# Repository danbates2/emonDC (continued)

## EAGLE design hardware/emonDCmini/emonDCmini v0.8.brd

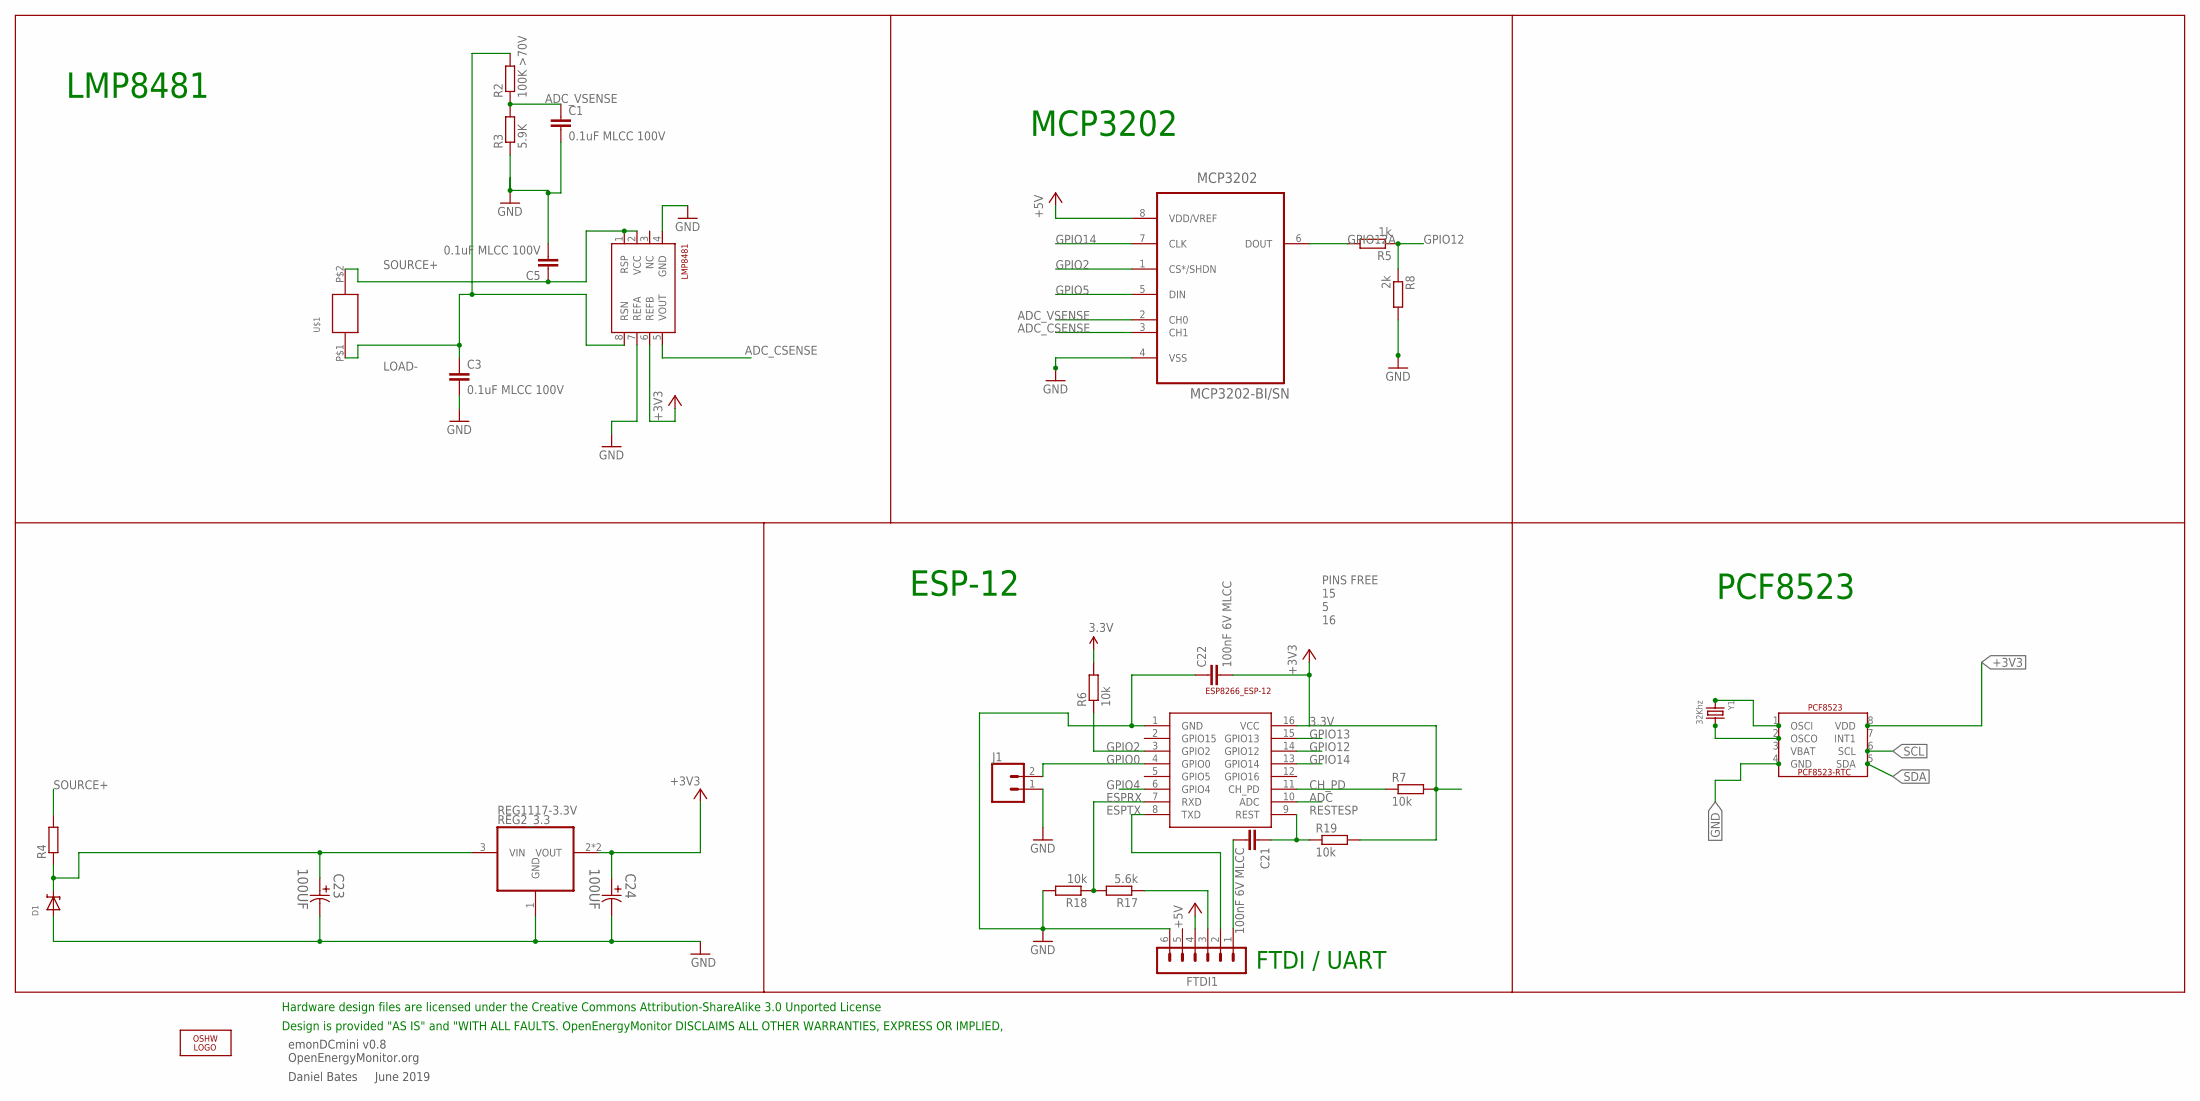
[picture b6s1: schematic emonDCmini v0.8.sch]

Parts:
C1, C3, C5: 0.1uF MLCC 100V; C0805
C21, C22: 100nF 6V MLCC; C0805
C23, C24: 100UF; CAPAE530X610N
D1: DIODE-ZENER; SMADIODE
ESP-12: ESP8266_ESP-12; ESP8266-ESP12
FTDI1: FTDI-ESP; MA06-1
J1: CONN_02; 1X02
LMP8481: LMP8481-H; S-PDSO-G08
LOGO1: OSHW_LOGO_6MILX0200-NT; OSHW_6X200_NOTEXT
MCP3202: MCP3202-BI/SN; SOIC127P600X175-8N
PCF8523: PCF8523_RTC; SOIC_8
R2: 100K >70V; R0603; MPN MCWR06X1003FTL
R3: 5.9K; R0603; MPN MCWR06X5901FTL
R4: R-EU_R2512; R2512
R5: 1k; R0603
R6, R7, R18, R19: 10k; R0603
R8: 2k; R0603
R17: 5.6k; R0603
REG2_3.3: REG1117-3.3V; SOT223; MPN REG1117-3.3
U$1: EBW_SERIES_10.5MM
Y1: 32Khz; CRYSTAL_8X3.8

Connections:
3.3V: C22.2, ESP-12.16 (VCC), LMP8481.6 (REFB), R6.2, R7.2, R19.2
6.5V: C23.1, D1.C, R4.1, REG2_3.3.3 (VIN)
+3V3: C24.1, PCF8523.8 (VDD), REG2_3.3.2 (VOUT), REG2_3.3.4 (VOUT)
+5V: FTDI1.4, MCP3202.8 (VDD/VREF)
ADC: ESP-12.10 (ADC)
ADC_CSENSE: LMP8481.5 (VOUT), MCP3202.3 (CH1)
ADC_VSENSE: C1.1, MCP3202.2 (CH0), R2.1, R3.2
CH_PD: ESP-12.11 (CH_PD), R7.1
ESPRX: ESP-12.7 (RXD), R17.2, R18.1
ESPTX: ESP-12.8 (TXD), FTDI1.2
GND: C1.2, C3.2, C5.2, C22.1, C23.2, C24.2, D1.A, ESP-12.1 (GND), FTDI1.6, J1.1, LMP8481.4 (GND), LMP8481.7 (REFA), MCP3202.4 (VSS), PCF8523.4 (GND), R3.1, R8.2, R18.2, REG2_3.3.1 (GND)
GPIO0: ESP-12.4 (GPIO0), J1.2
GPIO2: ESP-12.3 (GPIO2), MCP3202.1 (CS*/SHDN), R6.1
GPIO4: ESP-12.6 (GPIO4)
GPIO5: MCP3202.5 (DIN)
GPIO12: ESP-12.14 (GPIO12), R5.1, R8.1
GPIO12A: MCP3202.6 (DOUT), R5.2
GPIO13: ESP-12.15 (GPIO13)
GPIO14: ESP-12.13 (GPIO14), MCP3202.7 (CLK)
LOAD-: C3.1, LMP8481.8 (RSN), R2.2, U$1.P$1
unnamed: FTDI1.3, R17.1
unnamed: PCF8523.2 (OSCO), Y1.P$4 (2)
unnamed: PCF8523.1 (OSCI), Y1.P$1 (1)
RESTESP: C21.1, ESP-12.9 (REST), R19.1
RST: C21.2, FTDI1.1
SCL: PCF8523.6 (SCL)
SDA: PCF8523.5 (SDA)
SOURCE+: C5.1, LMP8481.1 (RSP), LMP8481.2 (VCC), R4.2, U$1.P$2

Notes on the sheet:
emonDCmini v0.8 OpenEnergyMonitor.org
Daniel Bates June 2019
Design is provided "AS IS" and "WITH ALL FAULTS. OpenEnergyMonitor DISCLAIMS ALL OTHER WARRANTIES, EXPRESS OR IMPLIED,
Hardware design files are licensed under the Creative Commons Attribution-ShareAlike 3.0 Unported License
LMP8481
ESP-12
PINS FREE 15 5 16
MCP3202
FTDI / UART
PCF8523

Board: 2 copper layers, 29 parts (9 on the bottom side), 22 nets, no tracks yet.

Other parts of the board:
U$3: DRAGON_LOGO_NOTEXT

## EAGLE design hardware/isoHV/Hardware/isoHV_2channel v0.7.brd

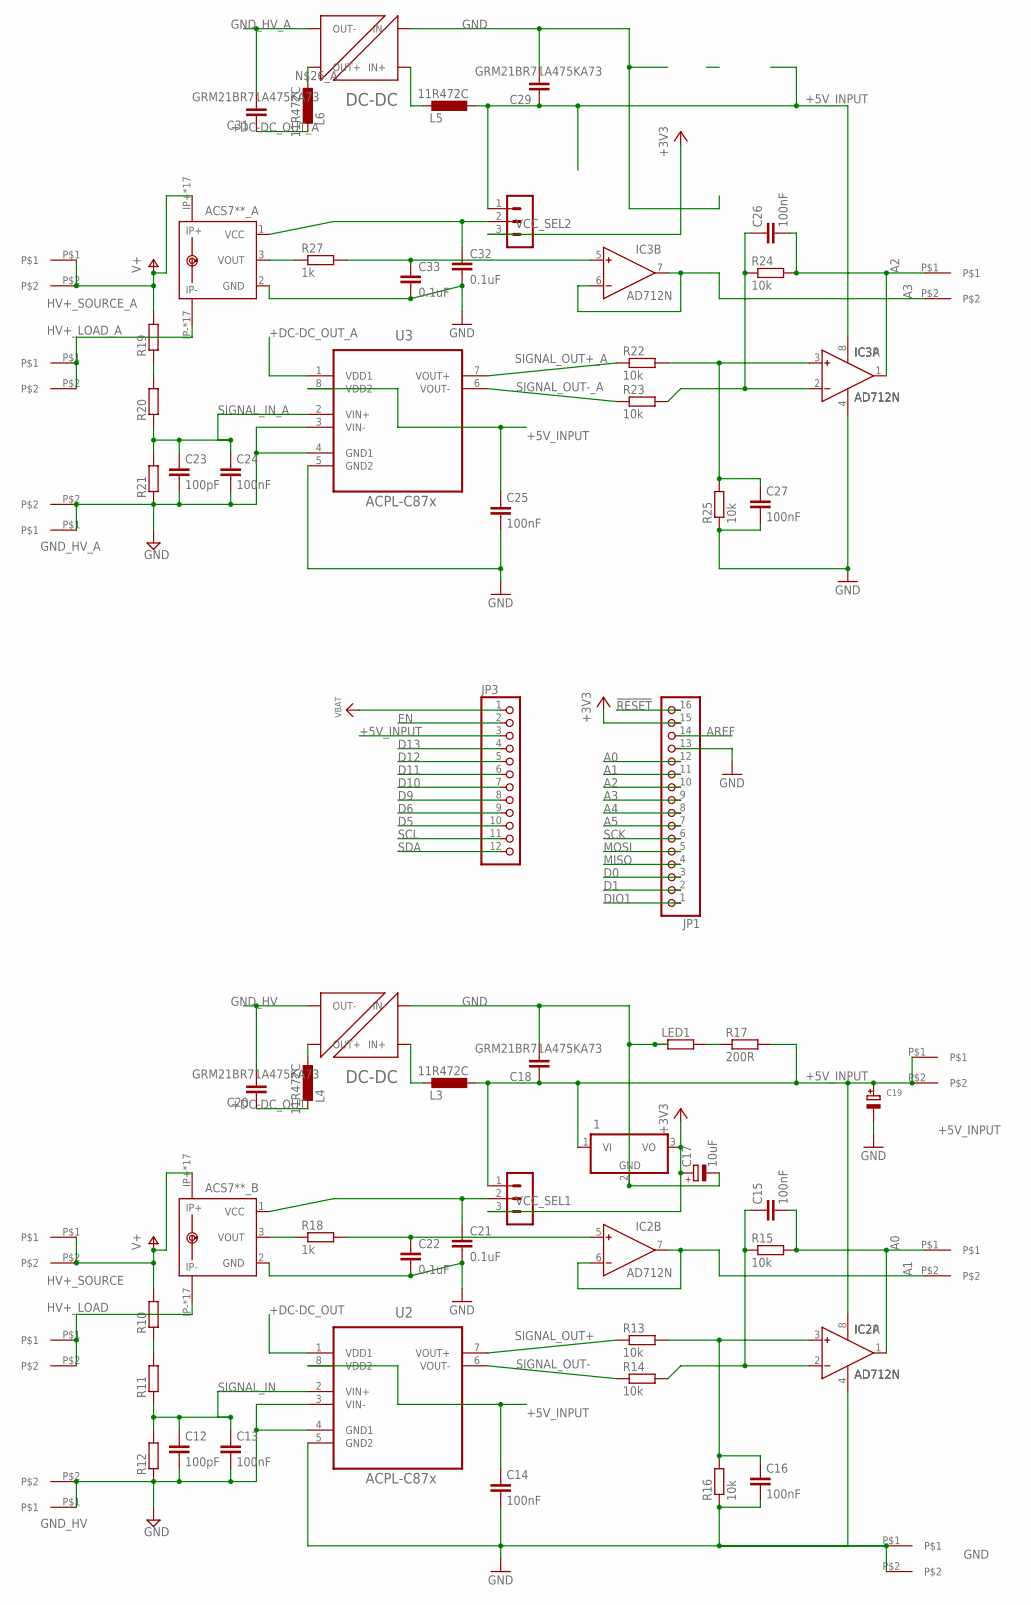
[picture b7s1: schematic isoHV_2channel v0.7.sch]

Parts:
1: 7805TV; TO220V
ACS7**_A, ACS7**_B: ACS758KCB-150B-PFF-T; CB-PFF; MPN ACS7**
C12, C23: 100pF; C025-025X050
C13, C14, C15, C16, C24, C25, C26, C27: 100nF; C025-025X050
C17: 10uF; B45181A
C18, C29: GRM21BR71A475KA73; C025-025X050
C19: CAP_ELECTROLYTICPTH_3.5MMGRID_10MMDIA; CELEC_3.5MM_10MM
C20, C31: GRM21BR71A475KA73; C025-050X050
C21, C22, C32, C33: 0.1uF; C025-025X050
IC2, IC3: AD712N; DIL08
JP1: HEADER-1X16ROUND; 1X16_ROUND
JP3: HEADER-1X12; 1X12_ROUND
L3, L4, L5, L6: 11R472C; 0204V
LED1: R-EU_0204/2V; 0204V
R10, R11, R12, R19, R20, R21: R-EU_0411/15; 0411/15
R13, R14, R15, R16, R22, R23, R24, R25: 10k; 0204/7
R17: 200R; 0204V
R18, R27: 1k; 0204/7
U2, U3: ACPL-C87x; SOIC127P1150X330-8N
U$8, U$9, U$10, U$14, U$15, U$16, U$21, U$22, U$25, U$26: 7.62MM_TERMINAL_BLOCK; 7.62MM
U$17, U$27: NXF1
VCC_SEL1, VCC_SEL2: MA03-1

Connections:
!RESET: JP1.16
+3V3: 1.3 (VO), C17.+, JP1.15, VCC_SEL1.3, VCC_SEL2.3
+5V_INPUT: 1.1 (VI), C14.1, C18.1, C19.+, C25.1, C29.1, IC2.8 (V+), IC3.8 (V+), JP3.3, L3.2, L5.2, R17.2, U2.8 (VDD2), U3.8 (VDD2), U$10.P$1, U$10.P$2, VCC_SEL1.1, VCC_SEL2.1
+DC-DC_OUT: C20.1, L4.1, U2.1 (VDD1)
+DC-DC_OUT_A: C31.1, L6.1, U3.1 (VDD1)
A0: C15.2, IC2.1 (OUT), JP1.12, R15.2, U$15.P$1
A1: IC2.6 (IN-), IC2.7 (OUT), JP1.11, U$15.P$2
A2: C26.2, IC3.1 (OUT), JP1.10, R24.2, U$25.P$1
A3: IC3.6 (IN-), IC3.7 (OUT), JP1.9, U$25.P$2
A4: JP1.8
A5: JP1.7
AREF: JP1.14
D0: JP1.3
D1: JP1.2
D5: JP3.10
D6: JP3.9
D9: JP3.8
D10: JP3.7
D11: JP3.6
D12: JP3.5
D13: JP3.4
DIO1: JP1.1
EN: JP3.2
GND: 1.2 (GND), ACS7**_A.2 (GND), ACS7**_B.2 (GND), C14.2, C16.2, C17.-, C18.2, C19.-, C21.2, C22.2, C25.2, C27.2, C29.2, C32.2, C33.2, IC2.4 (V-), IC3.4 (V-), JP1.13, LED1.1, R16.1, R25.1, U2.5 (GND2), U3.5 (GND2), U$14.P$1, U$14.P$2, U$17.P$1 (IN-), U$27.P$1 (IN-)
GND_HV: C12.2, C13.2, C20.2, R12.1, U2.3 (VIN-), U2.4 (GND1), U$9.P$1, U$9.P$2, U$17.P$7 (OUT-)
GND_HV_A: C23.2, C24.2, C31.2, R21.1, U3.3 (VIN-), U3.4 (GND1), U$22.P$1, U$22.P$2, U$27.P$7 (OUT-)
HV+_LOAD: ACS7**_B.IP-, ACS7**_B.IP-@2 (IP-), ACS7**_B.IP-@3 (IP-), ACS7**_B.IP-@4 (IP-), ACS7**_B.IP-@5 (IP-), ACS7**_B.IP-@6 (IP-), ACS7**_B.IP-@7 (IP-), ACS7**_B.IP-@8 (IP-), ACS7**_B.IP-@9 (IP-), ACS7**_B.IP-@10 (IP-), ACS7**_B.IP-@11 (IP-), ACS7**_B.IP-@12 (IP-), ACS7**_B.IP-@13 (IP-), ACS7**_B.IP-@14 (IP-), ACS7**_B.IP-@15 (IP-), ACS7**_B.IP-@16 (IP-), ACS7**_B.IP-@17 (IP-), U$16.P$1, U$16.P$2
HV+_LOAD_A: ACS7**_A.IP-, ACS7**_A.IP-@2 (IP-), ACS7**_A.IP-@3 (IP-), ACS7**_A.IP-@4 (IP-), ACS7**_A.IP-@5 (IP-), ACS7**_A.IP-@6 (IP-), ACS7**_A.IP-@7 (IP-), ACS7**_A.IP-@8 (IP-), ACS7**_A.IP-@9 (IP-), ACS7**_A.IP-@10 (IP-), ACS7**_A.IP-@11 (IP-), ACS7**_A.IP-@12 (IP-), ACS7**_A.IP-@13 (IP-), ACS7**_A.IP-@14 (IP-), ACS7**_A.IP-@15 (IP-), ACS7**_A.IP-@16 (IP-), ACS7**_A.IP-@17 (IP-), U$26.P$1, U$26.P$2
HV+_SOURCE: ACS7**_B.IP+, ACS7**_B.IP+@2 (IP+), ACS7**_B.IP+@3 (IP+), ACS7**_B.IP+@4 (IP+), ACS7**_B.IP+@5 (IP+), ACS7**_B.IP+@6 (IP+), ACS7**_B.IP+@7 (IP+), ACS7**_B.IP+@8 (IP+), ACS7**_B.IP+@9 (IP+), ACS7**_B.IP+@10 (IP+), ACS7**_B.IP+@11 (IP+), ACS7**_B.IP+@12 (IP+), ACS7**_B.IP+@13 (IP+), ACS7**_B.IP+@14 (IP+), ACS7**_B.IP+@15 (IP+), ACS7**_B.IP+@16 (IP+), ACS7**_B.IP+@17 (IP+), R10.2, U$8.P$1, U$8.P$2
HV+_SOURCE_A: ACS7**_A.IP+, ACS7**_A.IP+@2 (IP+), ACS7**_A.IP+@3 (IP+), ACS7**_A.IP+@4 (IP+), ACS7**_A.IP+@5 (IP+), ACS7**_A.IP+@6 (IP+), ACS7**_A.IP+@7 (IP+), ACS7**_A.IP+@8 (IP+), ACS7**_A.IP+@9 (IP+), ACS7**_A.IP+@10 (IP+), ACS7**_A.IP+@11 (IP+), ACS7**_A.IP+@12 (IP+), ACS7**_A.IP+@13 (IP+), ACS7**_A.IP+@14 (IP+), ACS7**_A.IP+@15 (IP+), ACS7**_A.IP+@16 (IP+), ACS7**_A.IP+@17 (IP+), R19.2, U$21.P$1, U$21.P$2
MISO: JP1.4
MOSI: JP1.5
unnamed: R10.1, R11.2
unnamed: C16.1, IC2.3 (IN+), R13.2, R16.2
unnamed: C15.1, IC2.2 (IN-), R14.2, R15.1
unnamed: ACS7**_B.1 (VCC), C21.1, VCC_SEL1.2
unnamed: C22.1, IC2.5 (IN+), R18.2
unnamed: LED1.2, R17.1
unnamed: L3.1, U$17.P$3 (IN+)
unnamed: L4.2, U$17.P$8 (OUT+)
unnamed: ACS7**_B.3 (VOUT), R18.1
unnamed: R19.1, R20.2
unnamed: C27.1, IC3.3 (IN+), R22.2, R25.2
unnamed: C26.1, IC3.2 (IN-), R23.2, R24.1
unnamed: ACS7**_A.1 (VCC), C32.1, VCC_SEL2.2
unnamed: C33.1, IC3.5 (IN+), R27.2
unnamed: L5.1, U$27.P$3 (IN+)
unnamed: L6.2, U$27.P$8 (OUT+)
unnamed: ACS7**_A.3 (VOUT), R27.1
SCK: JP1.6
SCL: JP3.11
SDA: JP3.12
SIGNAL_IN: C12.1, C13.1, R11.1, R12.2, U2.2 (VIN+)
SIGNAL_IN_A: C23.1, C24.1, R20.1, R21.2, U3.2 (VIN+)
SIGNAL_OUT+: R13.1, U2.7 (VOUT+)
SIGNAL_OUT+_A: R22.1, U3.7 (VOUT+)
SIGNAL_OUT-: R14.1, U2.6 (VOUT-)
SIGNAL_OUT-_A: R23.1, U3.6 (VOUT-)
VBAT: JP3.1

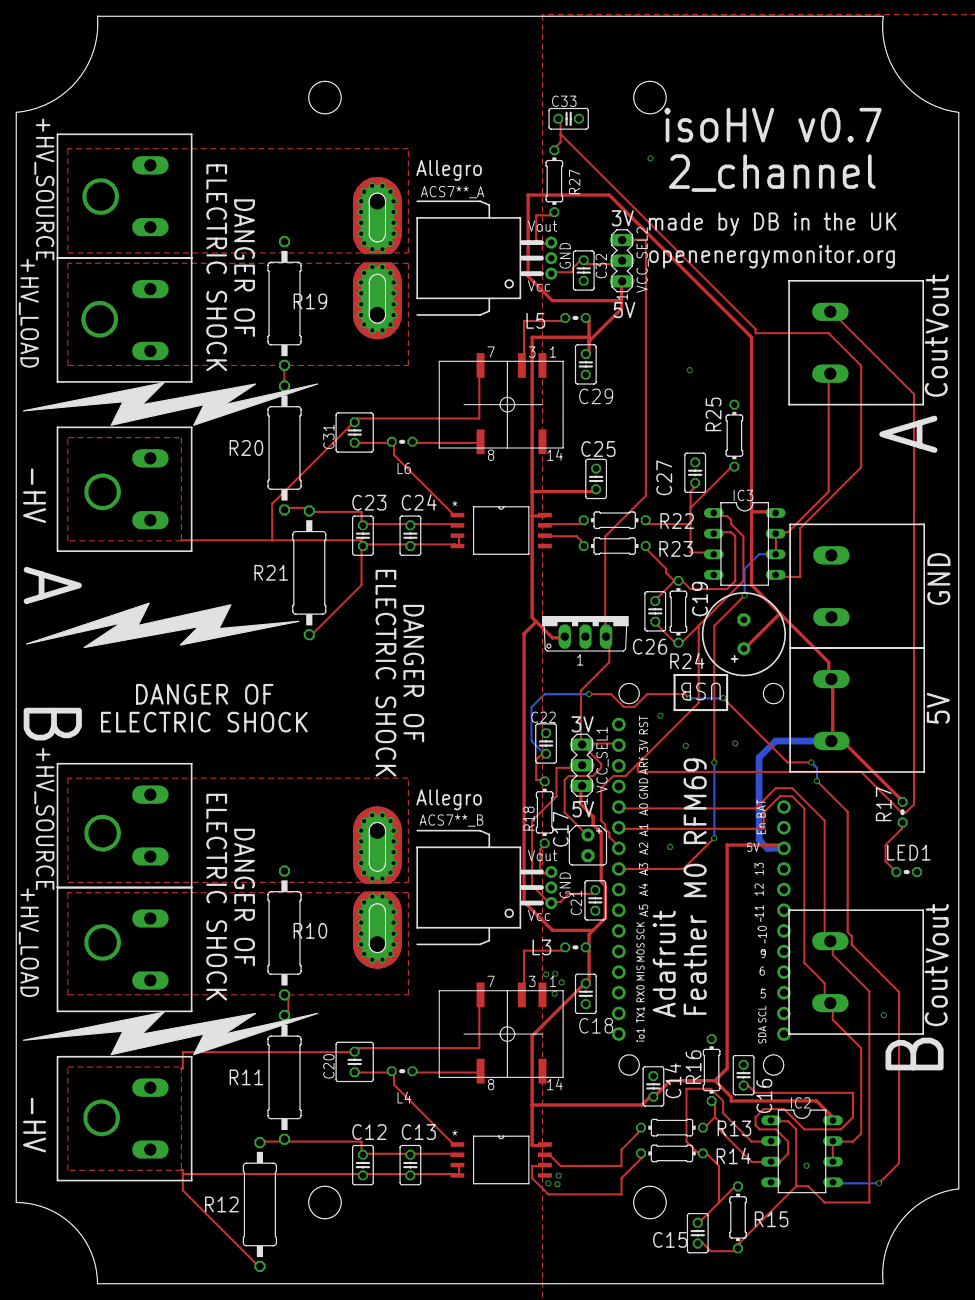
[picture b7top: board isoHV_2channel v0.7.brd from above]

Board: 2 copper layers, 116.0 x 156.0 mm, 65 parts (0 on the bottom side), 38 nets.

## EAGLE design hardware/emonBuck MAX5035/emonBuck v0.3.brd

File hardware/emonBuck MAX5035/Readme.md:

[https://community.openenergymonitor.org/t/dcduo-board-update/9189/13](https://community.openenergymonitor.org/t/dcduo-board-update/9189/13)

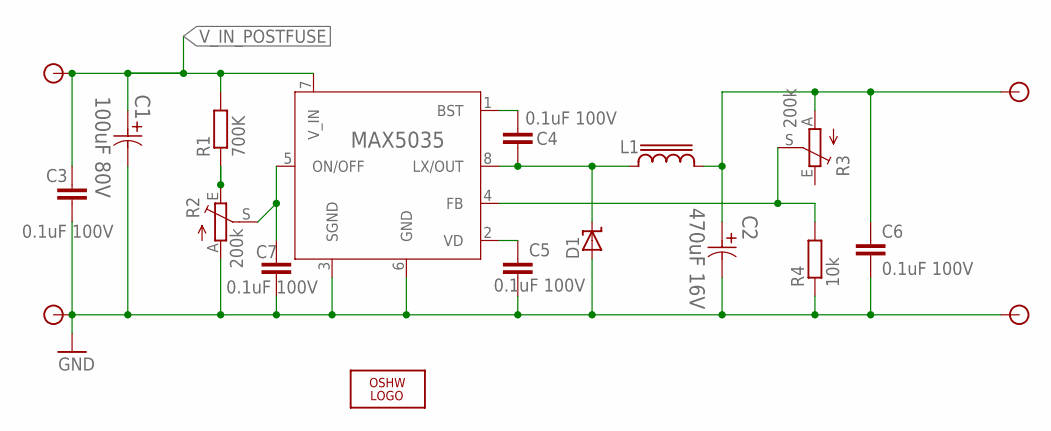
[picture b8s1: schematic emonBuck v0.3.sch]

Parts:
C1: 100uF 80V; CAPAE1350X1400N
C2: 470uF 16V; CAPAE830X1050N
C3, C4, C5, C6, C7: 0.1uF 100V; C0603
D1: MBRS1100T3G; SMB_1; MPN MBRS1100T3G
L1: SRR1208; SSR1208; MPN SRR1208-151YL
LOGO1: OSHW_LOGO_6MILX0200-NT; OSHW_6X200_NOTEXT
MAX5035: MAX5035; 21-0111D_SBE-14; MPN MAX5035EASA+
R1: 700K; R0603
R2, R3: 200k; B64W
R4: 10k; R0603
U$1, U$2, U$3, U$4: TP0.8MM; TP0.8

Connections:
BST: C4.1, MAX5035.1 (BST)
GND: C1.2, C2.2, C3.2, C5.2, C6.2, C7.2, D1.A, MAX5035.3 (SGND), MAX5035.6 (GND), R2.A, R4.1, U$2.P$1, U$4.P$1
LX: C4.2, D1.C, L1.1, MAX5035.8 (LX/OUT)
unnamed: MAX5035.4 (FB), R3.S, R4.2
unnamed: C7.1, MAX5035.5 (ON/OFF), R2.S
unnamed: R1.1, R2.E
PRE_6.5V: C2.1, C6.1, L1.2, R3.A, U$3.P$1
VD: C5.1, MAX5035.2 (VD)
V_IN_POSTFUSE: C1.1, C3.1, MAX5035.7 (V_IN), R1.2, U$1.P$1

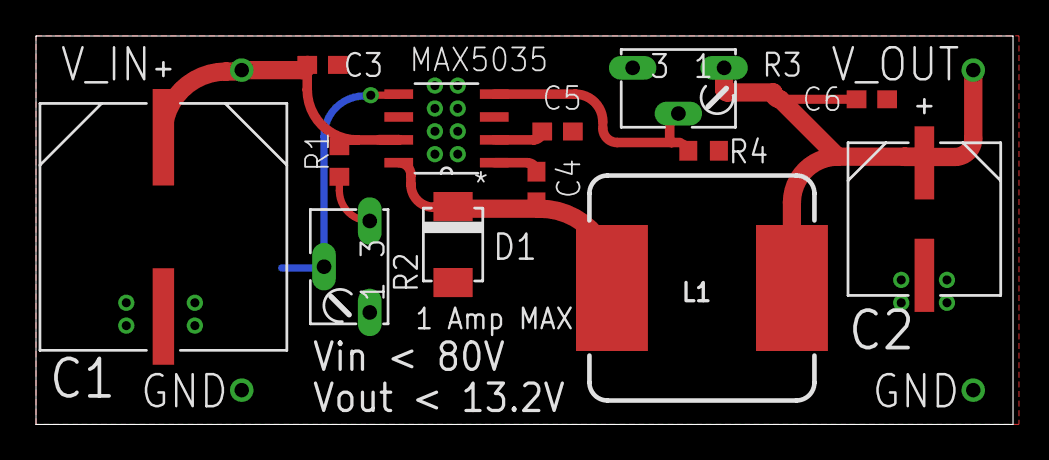
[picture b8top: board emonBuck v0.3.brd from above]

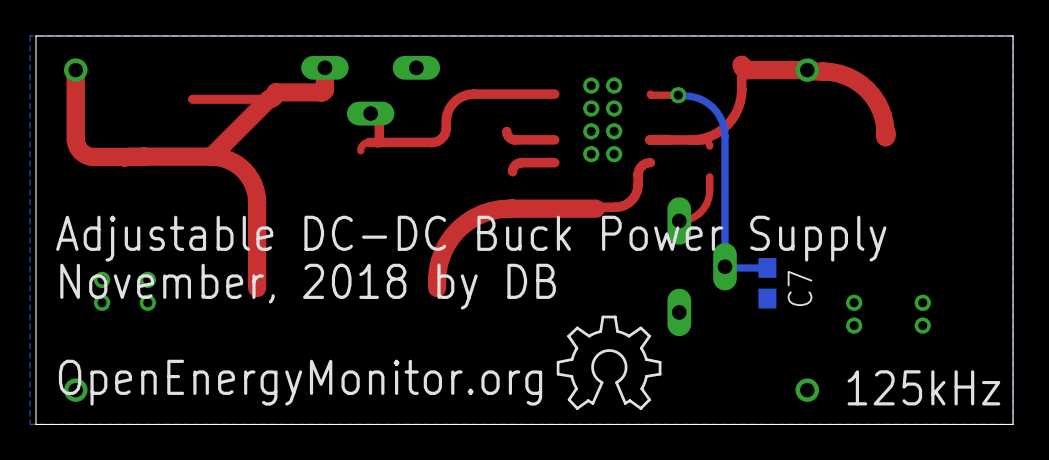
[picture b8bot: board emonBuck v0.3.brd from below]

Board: 2 copper layers, 54.3 x 21.6 mm, 19 parts (2 on the bottom side), 9 nets.

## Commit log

2016-12-15 emonDCuno
    unidirectional single input high voltage emonDC
2016-12-15 duo1
2016-12-15 foldertest
2016-12-15 folder update
2016-12-19 updating
2016-12-23 ESP addition and dual shunt monitors
2016-12-26 SD CARD TO DUO
2016-12-26 short write protect pins
2016-12-27 micro sd card library
    pinout in schematic TBD
2017-01-03 board layout changes
2017-01-03 images attached
2017-01-05 RFM69 onto board
2017-01-06 layout changes
2017-01-07 DRC edited
2017-01-08 antenna caps removed. camexport
2017-01-09 gerber
2017-01-09 refinement
2017-01-28 emonDCbike design first draft
2017-01-28 image export
2017-02-16 updating v1.0
2017-03-18 added DIP switch to ESP RX/TX
2017-03-29 emonBIKE v0.2 camexport
2017-03-29 tidy
2017-04-05 emonBike v0.3
2017-05-23 src commit
2017-06-14 emonDCmini v0.4 sent to ragworm
2017-06-17 update
    chip select set to GPIO4 for both mini and duo.
    mini updated, various minor changes for v0.5.
    molex micro sd card library improved
2017-07-28 v0.6 camexport and prototype sent
2017-07-30 v1.0 duo camexport and prototype
2017-10-09 new boards and library files
2017-10-09 deleted libs
2017-12-13 commit v1.3c
2017-12-14 commit v1.3c update
2017-12-14 commit v1.1c update
2018-03-27 reorder files, deletion and archive
2018-03-27 Set theme jekyll-theme-slate
2018-03-28 unzip firmware
2018-03-28 reorder folders
2018-03-30 v1.4 changes. firmware dev.
2018-04-06 readme updated
2018-08-01 v2.3
2018-10-24 commit v3.0 WIP
2018-11-09 starting v3.0 and ASC770 breakout
2018-11-15 commit v3.0
2018-11-16 commit v3.1
2018-11-28 commit v3.2
2018-12-06 commit v3.3
    added temp sensor
2018-12-06 commit v3.4
    curvy corners!
2018-12-06 commit v3.4
2018-12-09 commit v3.5 & 3dprintable case
2018-12-12 commit v3.5
2018-12-19 commit test
2018-12-19 copmmity
2019-02-19 commit v3.7
2019-02-20 readme
2019-03-25 new images, updated readme
2019-03-26 images
2019-03-29 shoot1
2019-03-29 sharpen images
2019-03-30 acs7** addition, emonBuck update
2019-04-02 arp2019 firmware
2019-04-05 update readme and pics
2019-04-08 apr2019_2 firmwazre
2019-04-09 commit draft DC doco
2019-04-09 draft commit
2019-04-11 commit doco v1.3
2019-04-13 commit v4.0
2019-04-16 update Doco
2019-04-23 commit v4.1
2019-04-27 commit v4.1
    HV isolation improvements
2019-05-27 firmware update
2019-07-02 July 2019 firmware
2019-07-09 isoHV and emonDCmini added
2019-09-30 isoHV firmware update
2019-09-30 commit image
2019-10-23 commit SEP2019 firmware
2019-12-05 amended firmware.
2020-02-28 RTC and NTP time working
2020-02-29 minor fix, notes added
2020-03-03 SD card working
2020-03-04 web interface addition for calibration
2020-03-04 old board additions
2020-03-05 emonDC-related settings in SPIFFS as JSON file.
    src/data/emondc_settings.json
2020-03-05 long long accumulators, just in case.
2020-03-05 march.
2020-03-06 amplifier offset correction values added
2020-03-09 code tidy, amp hours
2020-03-29 update
    maaaany fixes.
    State of Charge battery monitoring first draft.
2020-04-02 progmem settings, captive portal
2020-04-03 SoC fix
2020-04-06 oled graphics, web interface improvement
2020-06-10 report min and max voltage and current each reporting interval
2020-06-18 automatically create web_server_files
    embedding hex using a C program, run with a bash script automatically. tested on macOS only.
2020-11-26 sync stm32 v0.2
